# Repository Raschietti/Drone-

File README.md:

# Drone-
There are several codes on the internet for drone control, but there is not much to learn by just copying and pasting code, In this project I will try to explain each step I did to write a code and Hardware project of a simple drone with cheap parts

# Hardware

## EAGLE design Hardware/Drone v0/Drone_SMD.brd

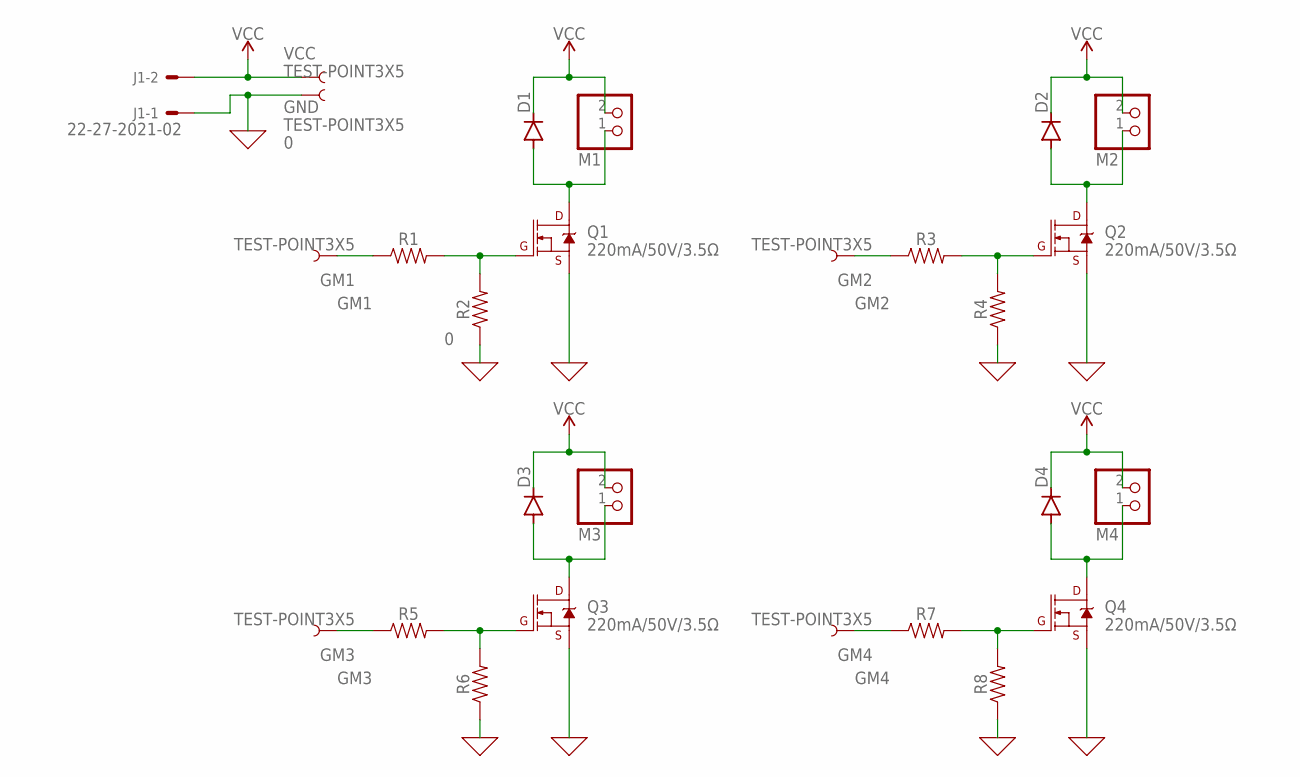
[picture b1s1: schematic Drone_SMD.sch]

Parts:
D1, D2, D3, D4: DIODE-DO-214AC; DO-214AC
GM1, GM2, GM3, GM4: TEST-POINT3X5; PAD.03X.05
GND: TEST-POINT3X5; PAD.03X.05
J1: 22-27-2021-02; 6410-02
M1, M2, M3, M4: PINHD-1X2; 1X02
Q1, Q2, Q3, Q4: 220mA/50V/3.5Ω; SOT23-3
R1, R2, R3, R4, R5, R6, R7, R8: 1206
VCC: TEST-POINT3X5; PAD.03X.05

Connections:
0: GND.1, J1.1, Q1.2 (S), Q2.2 (S), Q3.2 (S), Q4.2 (S), R2.1, R4.1, R6.1, R8.1
GM1: GM1.1, R1.1
GM2: GM2.1, R3.1
GM3: GM3.1, R5.1
GM4: GM4.1, R7.1
unnamed: Q1.1 (G), R1.2, R2.2
unnamed: D1.A, M1.1, Q1.3 (D)
unnamed: Q2.1 (G), R3.2, R4.2
unnamed: D2.A, M2.1, Q2.3 (D)
unnamed: Q3.1 (G), R5.2, R6.2
unnamed: D3.A, M3.1, Q3.3 (D)
unnamed: Q4.1 (G), R7.2, R8.2
unnamed: D4.A, M4.1, Q4.3 (D)
VCC: D1.C, D2.C, D3.C, D4.C, J1.2, M1.2, M2.2, M3.2, M4.2, VCC.1

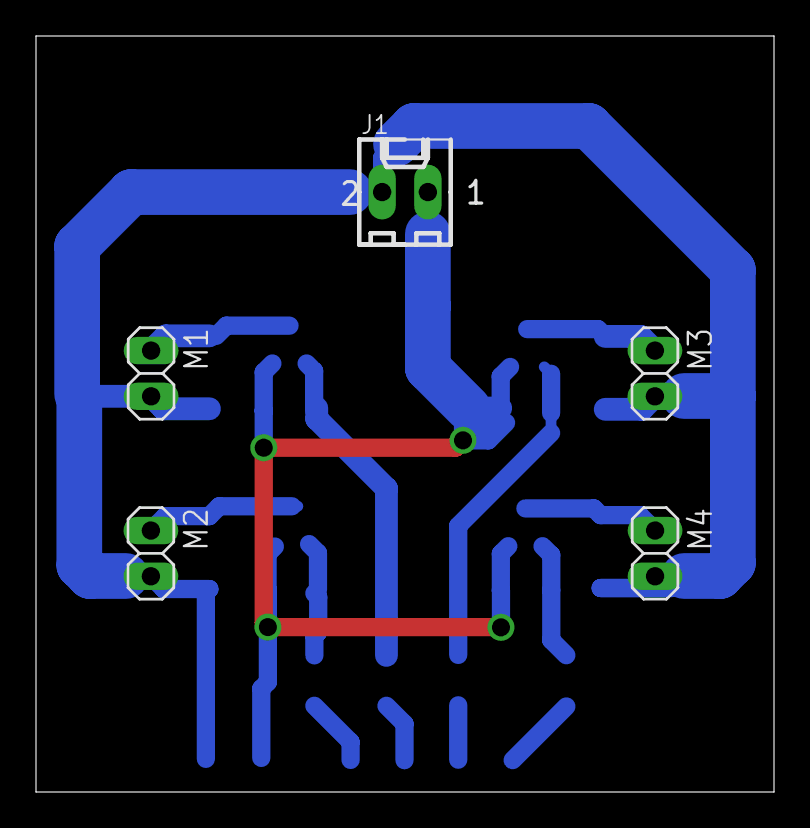
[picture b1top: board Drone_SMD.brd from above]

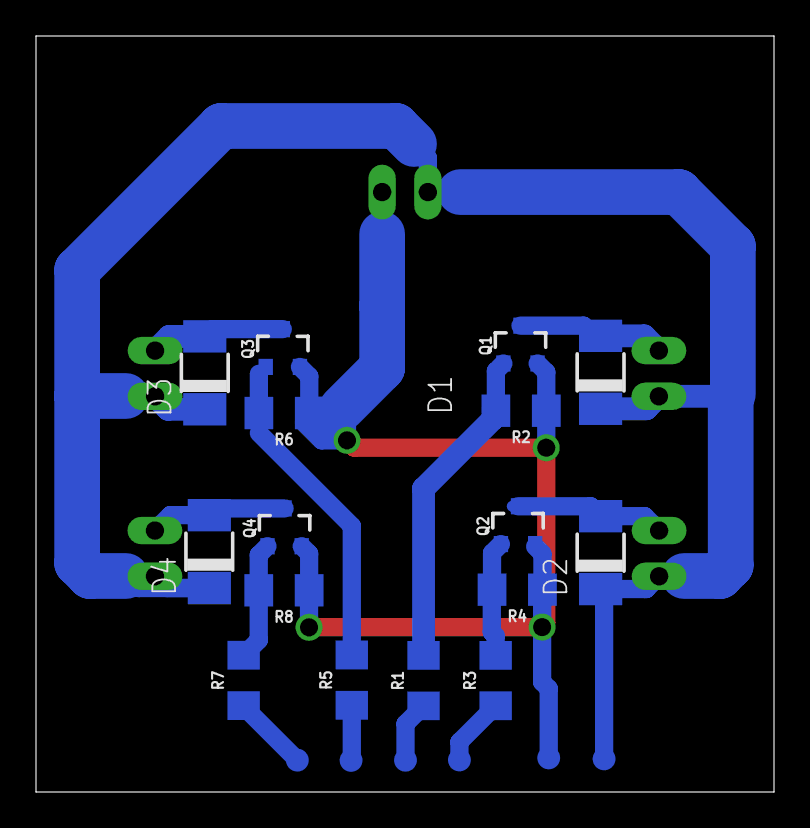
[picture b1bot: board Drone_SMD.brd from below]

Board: 2 copper layers, 41.0 x 42.0 mm, 27 parts (22 on the bottom side), 14 nets.

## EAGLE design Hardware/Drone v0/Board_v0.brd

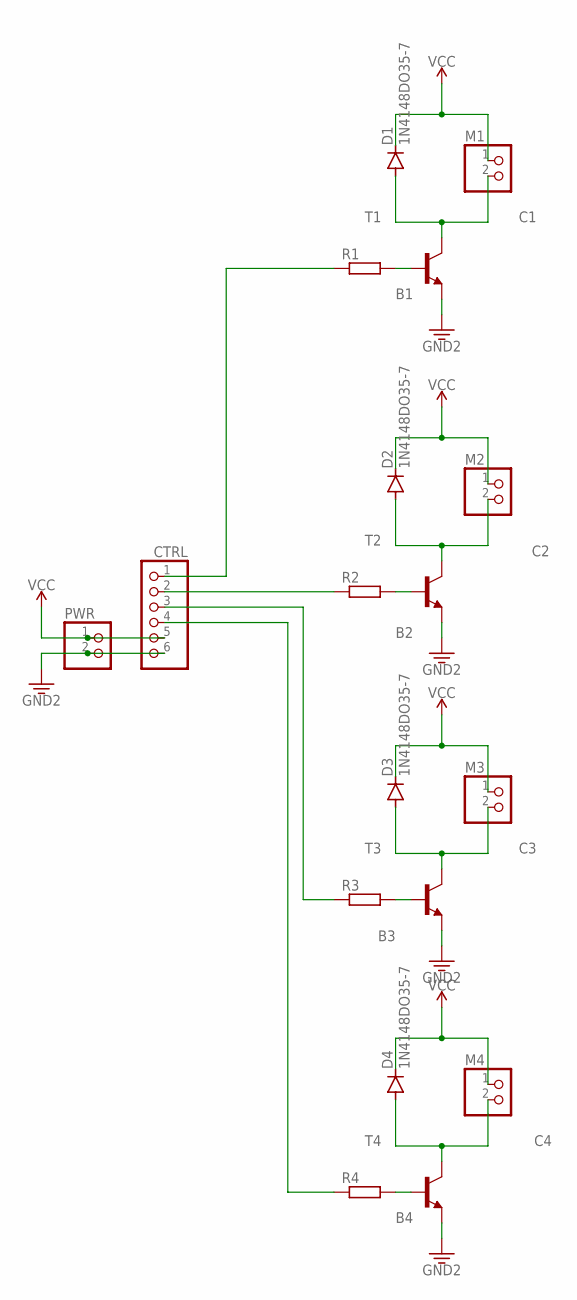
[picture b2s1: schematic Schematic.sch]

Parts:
CTRL: PINHD-1X6; 1X06
D1, D2, D3, D4: 1N4148DO35-7; DO35-7
M1, M2, M3, M4: PINHD-1X2; 1X02
PWR: PINHD-1X2; 1X02
R1, R2, R3, R4: R-EU_R0805; R0805
T1, T2, T3, T4: 2N2222-NPN-TO92-EBC; TO92-EBC

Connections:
3.3V: CTRL.6, PWR.2, T1.E, T2.E, T3.E, T4.E
B1: R1.2, T1.B
B2: R2.2, T2.B
B3: R3.2, T3.B
B4: R4.2, T4.B
C1: D1.A, M1.2, T1.C
C2: D2.A, M2.2, T2.C
C3: D3.A, M3.2, T3.C
C4: D4.A, M4.2, T4.C
unnamed: CTRL.1, R1.1
unnamed: CTRL.2, R2.1
unnamed: CTRL.3, R3.1
unnamed: CTRL.4, R4.1
VCC: CTRL.5, D1.C, D2.C, D3.C, D4.C, M1.1, M2.1, M3.1, M4.1, PWR.1

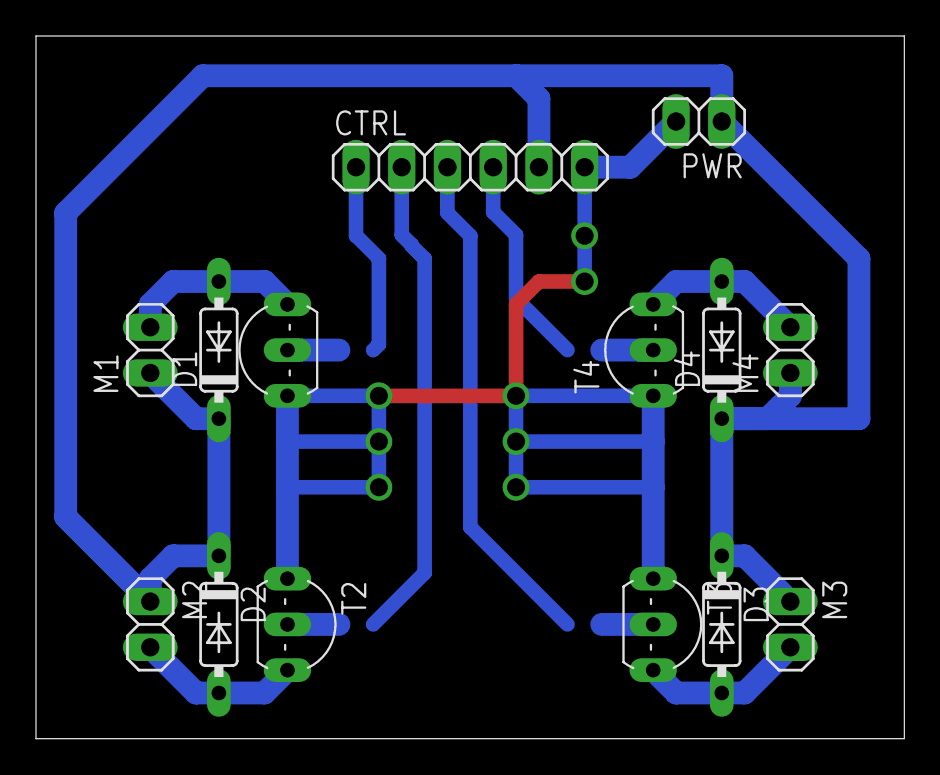
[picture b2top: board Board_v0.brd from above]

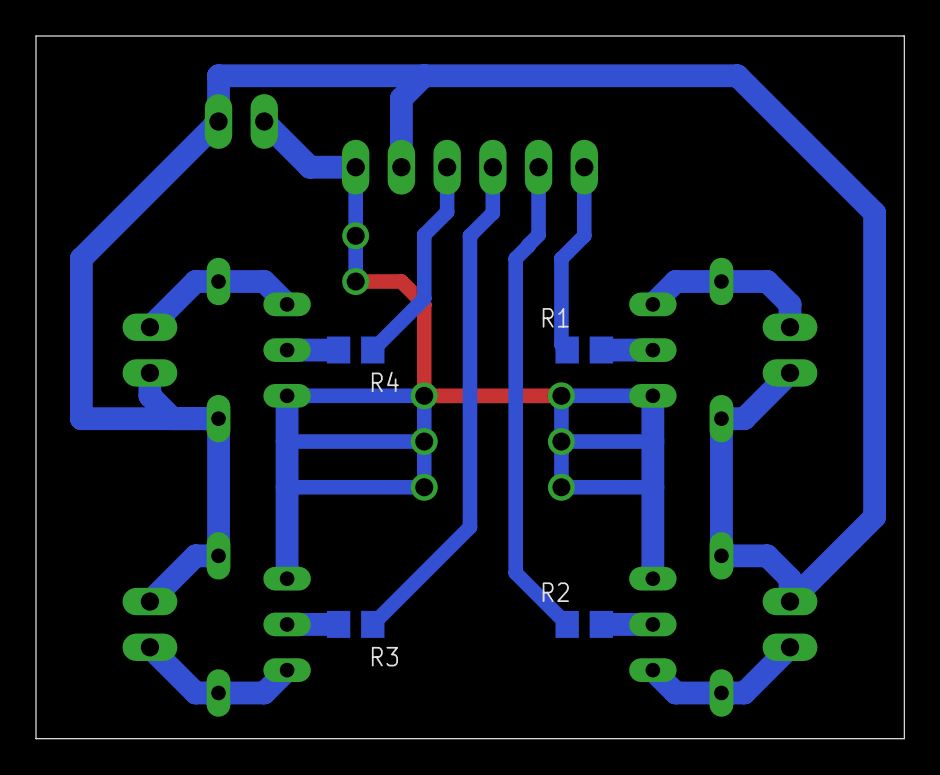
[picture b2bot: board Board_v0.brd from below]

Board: 2 copper layers, 48.2 x 39.0 mm, 18 parts (4 on the bottom side), 14 nets.

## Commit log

2023-01-27 Empty project added
2023-01-27 Add early hardware design PCB and Schematics
2023-01-27 Added hardware encapsulation files
2023-01-28 Added Functions to GPIO Drivers
2023-01-28 Add sensor encapsulation Drivers
2023-01-28 Push
2023-01-28 MPU Sensor driver implemented
2023-01-29 Driver GPIO Testado e Driver UART adicionado
2023-01-29 Sensor driver its not working properly
2023-02-01 Fixed sensor module

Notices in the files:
parts and their libraries:
SparkFun-Connectors: Licensing: Creative Commons ShareAlike 4.0 International - https://creativecommons.org/licenses/by-sa/4.0
